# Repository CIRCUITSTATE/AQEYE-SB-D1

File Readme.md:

# AQEYE-SB-D1

[**AQEYE-SB-D1**](https://github.com/CIRCUITSTATE/AQEYE-SB-D1) is a PCB designed to hold the sensors for the AQEYE-D1 Air Quality Monitor project by CIRCUITSTATE Electronics. The board is designed to be connected to either the [**ESP32-S3-Touch-LCD-2.8**](https://www.waveshare.com/esp32-s3-touch-lcd-2.8.htm) from Waveshare or the AQEYE-MB-D1 main board. A separate sensor board was designed to keep the sensitive components away from external interferences such as noise, heat and other effects. This also makes it easier to replace the sensors or to add new sensors in the future without having to redesign the main board. AQEYE-SB-D1 is a completely open-source hardware (OSHW) project designed in the **KiCad** open-source EDA tool. **SB** stands for Sensor Board and **D1** is the first design variant of this project. You can download the source files of this design, modify them and redistribute them as you wish.

## Features

- Sensors
  - **Asair DHT20** temperature and humidity sensor.
  - **Asair AGS02MA** TVOC (Total Volatile Organic Compounds) sensor.
  - **Winsen ZH06** PM (Particulate Matter) sensor with PM1.0, PM2.5, PM10 measurement.
  - **Sensirion SCD40-D-R2** CO2 (Carbon Dioxide) sensor.
  - **Sensirion SGP40-D-R4** TVOC sensor.
- Connectors and solderpads for all sensors.
- 12-pin JST-SH connector for connecting to the main board.
- Selectable I2C pull-up resistors.
- **TPS61023** +5V boost converter to generate 5V from the 3.3V input for sensors that require 5V.
  - Output controlled by a GPIO pin.
- **AP22804AW5** based +3.3V load switch to control the power.
  - Controlled by a GPIO pin.
  - Jumper pad to constant enable.
- **LM66100DCKR** ideal diode based voltage ORing selector and reverse polarity protection for the 5V rail.
- Power indication LEDs for both 3.3V and 5V rails.
- Four M2 mounting holes.

## Design

- **Parent Project:** AQEYE-SB
- **Variant:** [AQEYE-SB-D1](https://github.com/CIRCUITSTATE/AQEYE-SB-D1)
- **Author:** Vishnu Mohanan (@vishnumaiea, @vizmohanan)
- **Latest Revision:** `R0.1`
- **Layer Count:** 2
- **Thickness:** 1.6 mm
- **Dimensions:** 80 x 30 mm
- **EDA Tool:** KiCad V9
- **License:** MIT

## Contributing

If you would like to contribute this project, you are welcome to post issues and feature requests on the **Issues** page. If you fork this project and created a new variant, you can let us know about it and get a unique identifier assigned for your project. The ID takes the following form.

```
Y<digit><letter><digit>
```

`Y` – Constant prefix.

`<digit>` – Digits from 0–9

`<letter>` – Characters from A–Z.

**Examples:**

```
Y1A1
Y1A2
Y2B1
Y3C4
```

The forked project should then be renamed to `AQEYE-SB-D1-<ID>` form.

**Guidelines:**

- IDs are assigned upon request. You can create a new issue to request a new ID once a fork is created. Keep the issue title as `Request New ID` and include a link to your fork in the description.
- You can either request a new ID that you like and that is already not chosen, or allow us to choose an ID for you.
- You should rename the original source files with the `AQEYE-SB-D1-<ID>` format.
- On the PCB, you can place the name of the project as `AQEYE-SB-D1` and keep the ID as a standalone text on any visible layers.
- Once a unique ID is assigned to a forked project, the revision should be reset to `R0.1`. Do not keep the original revision of the project.

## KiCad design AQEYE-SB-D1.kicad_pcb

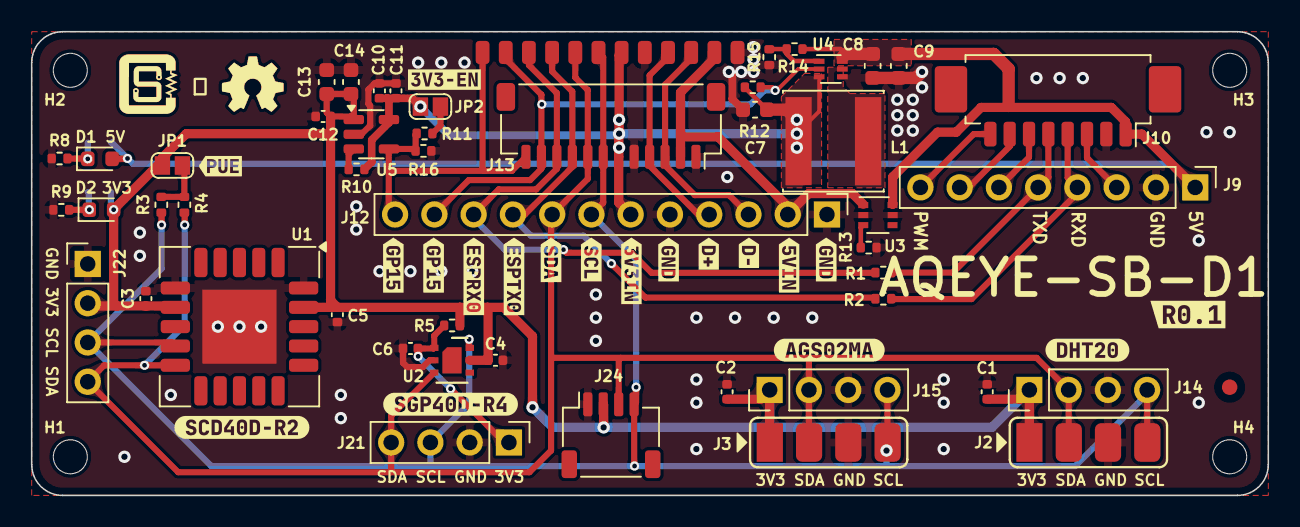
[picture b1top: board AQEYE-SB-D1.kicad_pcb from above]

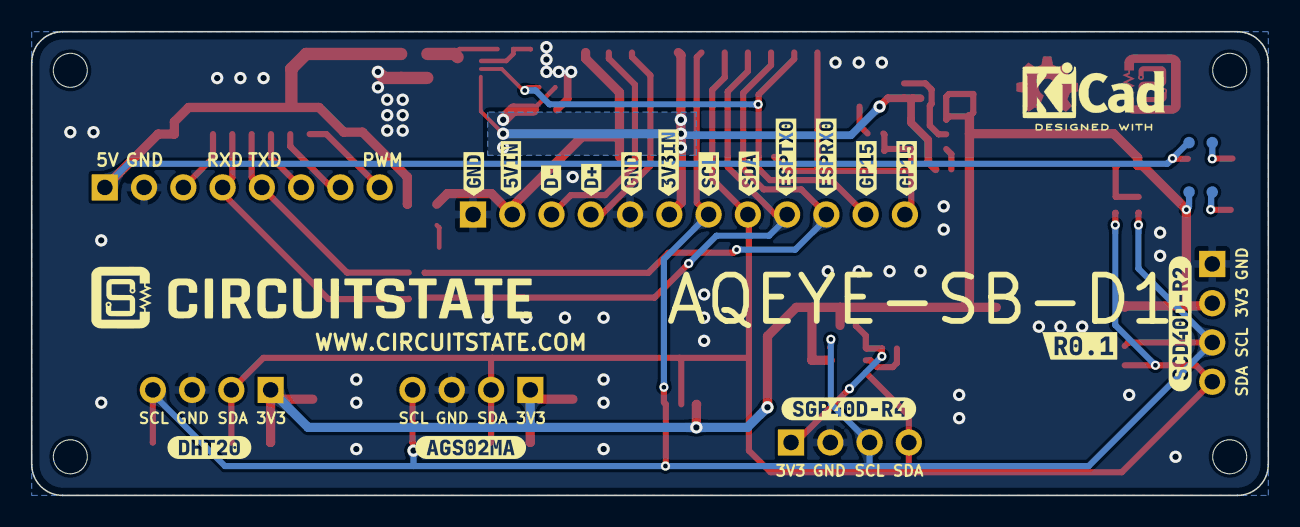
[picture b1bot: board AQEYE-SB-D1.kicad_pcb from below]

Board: 2 copper layers, 80.0 x 30.0 mm, 105 parts (21 on the bottom side), 24 nets.

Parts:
C1, C2, C3, C5, C10, C12: 0.1uF; C_0402_1005Metric
C4, C6, C11: 10uF; C_0402_1005Metric
C7, C8, C9, C13, C14: 22uF; C_0603_1608Metric
D1: 5V_LED; LED_0603_1608Metric
D2: 3V3_LED; LED_0603_1608Metric
H1, H2, H3, H4: Mounting Hole; MountingHole_2.2mm_M2_DIN965
J1: GPIO15; Solderpad_Rounded_Rectangle_0.9x1.5mm
J2: DHT20_PAD; Solderpad_1x04_P2.54mm_Rounded_Rectangle
J3: AGS02MA_PAD; Solderpad_1x04_P2.54mm_Rounded_Rectangle
J4: GPIO18; Solderpad_Rounded_Rectangle_0.9x1.5mm
J5: ESP_RXD0; Solderpad_Rounded_Rectangle_0.9x1.5mm
J6: ESP_TXD0; Solderpad_Rounded_Rectangle_0.9x1.5mm
J7: I2C_SDA; Solderpad_Rounded_Rectangle_0.9x1.5mm
J8: I2C_SCL; Solderpad_Rounded_Rectangle_0.9x1.5mm
J9: ZH06_Pin; PinHeader_1x08_P2.54mm_Vertical
J10: ZH06_PicoBlade; Molex_PicoBlade_53261-0871_1x08-1MP_P1.25mm_Horizontal
J11: +3.3V; Solderpad_Rounded_Rectangle_0.9x1.5mm
J12: MB_PINS; PinHeader_1x12_P2.54mm_Vertical
J13: MB_CONNECTOR; JST_SH_SM12B-SRSS-TB_1x12-1MP_P1.00mm_Horizontal
J14: DHT20; PinHeader_1x04_P2.54mm_Vertical
J15: AGS02MA; PinHeader_1x04_P2.54mm_Vertical
J16, J20: GND; Solderpad_Rounded_Rectangle_0.9x1.5mm
J17: USB_D+; Solderpad_Rounded_Rectangle_0.9x1.5mm
J18: USB_D-; Solderpad_Rounded_Rectangle_0.9x1.5mm
J19: +5V; Solderpad_Rounded_Rectangle_0.9x1.5mm
J21: SGP40-D-R4_CONN; PinHeader_1x04_P2.54mm_Vertical
J22: SCD40-D-R2_CONN; PinHeader_1x04_P2.54mm_Vertical
J24: STEMMA-QT; JST_SH_SM04B-SRSS-TB_1x04-1MP_P1.00mm_Horizontal_2
JP1: I2C_PUE; Solder-Jumper-1x2_P1.3mm_Open_Rounded_1.0x1.2mm
JP2: 3V3_EN; Solder-Jumper-1x2_P1.3mm_Open_Rounded_1.0x1.2mm
L1: 1uH; L_Changjiang_FNR6020S
R1, R2, R11: 1K; R_0402_1005Metric
R3, R4: 5.1K; R_0402_1005Metric
R5: 4.7R; R_0402_1005Metric
R8: 330R; R_0402_1005Metric
R9: 220R; R_0402_1005Metric
R10, R12, R13, R16: 10K; R_0402_1005Metric
R14: 732K; R_0402_1005Metric
R15: 100K; R_0402_1005Metric
TP1: 5V_LED_P; TestPoint-0.75mm
TP2: 5V_LED_M; TestPoint-0.75mm
TP3: 3V3_LED_P; TestPoint-0.75mm
TP4: 3V3_LED_M; TestPoint-0.75mm
U1: SCD40-D-R2; Sensirion_SCD4x-1EP_10.1x10.1mm_P1.25mm_EP4.8x4.8mm
U2: SGP40-D-R4; DFN-6-1EP_2.44x2.44mm_P0.8mm_EP1.25x1.7mm
U3: LM66100DCKR; SOT-363_SC-70-6
U4: TPS61023; SOT-563
U5: AP22804AW5; SOT-23-5
kibuzzard-68408B8A, kibuzzard-68408B8A#2: G***; kibuzzard-68408B8A
kibuzzard-68408BAF, kibuzzard-68408BAF#2: G***; kibuzzard-68408BAF
kibuzzard-68408BD4, kibuzzard-68408BD4#2: G***; kibuzzard-68408BD4
kibuzzard-68408D06, kibuzzard-68408D06#2: G***; kibuzzard-68408D06
kibuzzard-68408D87, kibuzzard-68408D87#2: G***; kibuzzard-68408D87
kibuzzard-68408E5C: G***; kibuzzard-68408E5C
kibuzzard-68408E86: G***; kibuzzard-68408E86
kibuzzard-684088E7, kibuzzard-684088E7#2, kibuzzard-684088E7#3, kibuzzard-684088E7#4: G***; kibuzzard-684088E7
kibuzzard-6840890A, kibuzzard-6840890A#2, kibuzzard-6840890A#3, kibuzzard-6840890A#4: G***; kibuzzard-6840890A
kibuzzard-6840894F, kibuzzard-6840894F#2: G***; kibuzzard-6840894F
kibuzzard-6840895D, kibuzzard-6840895D#2: G***; kibuzzard-6840895D
kibuzzard-68408942, kibuzzard-68408942#2: G***; kibuzzard-68408942
kibuzzard-68408956, kibuzzard-68408956#2: G***; kibuzzard-68408956
kibuzzard-68408963, kibuzzard-68408963#2: G***; kibuzzard-68408963
kibuzzard-68408966, kibuzzard-68408966#2: G***; kibuzzard-68408966
kibuzzard-68408979, kibuzzard-68408979#2: G***; kibuzzard-68408979
kibuzzard-68408981, kibuzzard-68408981#2: G***; kibuzzard-68408981

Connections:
+3.3V: C1.1, C2.1, C3.1, C4.1, C5.1, C12.1, C13.1, C14.1, D2.2 (A), J2.1, J3.1, J14.1, J15.1, J22.2, J24.2, JP1.1 (A), R5.1, TP3.1, U1.7 (VDD), U1.19 (VDD), U2.5 (VDDH), U5.1 (OUT)
+3.3V_IN: C7.1, C10.1, C11.1, J11.1, J12.6, J13.6, JP2.2 (B), L1.1, R10.2, R12.2, U4.3 (VIN), U5.5 (IN)
+5V: C8.1, C9.1, D1.2 (A), J9.1, J10.1, R14.2, TP1.1, U3.6 (VOUT), U4.6 (VOUT)
+5V_IN: J12.2, J13.2, J19.1, U3.1 (VIN)
/ESP_RXD0: J5.1, J12.10, J13.10, R1.2
/ESP_TXD0: J6.1, J12.9, J13.9, R2.2
/GPIO15: J1.1, J12.12, J13.12, R11.1, R16.2, U5.4 (EN)
/GPIO18: J4.1, J12.11, J13.11, R12.1, U4.2 (EN)
/I2C_SCL: J2.4, J3.4, J8.1, J12.7, J13.7, J14.4, J15.4, J21.3, J22.3, J24.4, R3.1, U1.9 (SCL), U2.6 (SCL)
/I2C_SDA: J2.2, J3.2, J7.1, J12.8, J13.8, J14.2, J15.2, J21.4, J22.4, J24.3, R4.1, U1.10 (SDA), U2.3 (SDA)
/USB_D+: J12.4, J13.4, J17.1
/USB_D-: J12.3, J13.3, J18.1
GND: C1.2, C2.2, C3.2, C4.2, C5.2, C6.1, C7.2, C8.2, C9.2, C10.2, C11.2, C12.2, C13.2, C14.2, J2.3, J3.3, J9.2, J10.2, J12.1, J12.5, J13.1, J13.5, J14.3, J15.3, J16.1, J20.1, J21.2, J22.1, J24.1, R8.1, R9.1, R13.1, R15.1, R16.1, U1.6 (GND), U1.20 (GND), U1.21 (GND), U2.2 (GND), U3.2 (GND), U3.5 (ST), U4.4 (GND), U5.2 (GND)
unnamed: D1.1 (K), R8.2, TP2.1
unnamed: D2.1 (K), R9.2, TP4.1
unnamed: J9.4, J10.4, R2.1
unnamed: J9.5, J10.5, R1.1
unnamed: C6.2, J21.1, R5.2, U2.1 (VDD)
unnamed: JP1.2 (B), R3.2, R4.2
unnamed: JP2.1 (A), R11.2
unnamed: R13.2, U3.3 (CE)
unnamed: R14.1, R15.2, U4.1 (FB)
unnamed: L1.2, U4.5 (SW)
unnamed: R10.1, U5.3 (~FLG)

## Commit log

2025-06-05 Initial commit
    - Schematic
    - Completed the schematic.
    - Assigned all footprints.
    - Added net classes and colors.
    - ERC passes.
    - PCB
2025-06-06 Generated manufacturing files
    - Schematic
    - Updated BoM.
    - Assigned all MPNs.
    - Added `Group by MPN-DNP` preset.
    - PCB
    - Imported all changes to the PCB.
2025-06-07 Added 5V boost converter
    - Schematic
    - Realized that the main board can not supply 5V when the USB is not connected.
    - Added a `TPS61023` 5V boost converter to generate 5V from the 3.3V input.
    - Removed the 5V load switch since the 5V output can not be controlled via the boost converter.
    - The 5V converter enabled by default with a GPIO control.
    - Added `LM66100DCKR` single-channel ideal diode to connect the VBUS to the 5V rail.
2025-06-15 Updated Readme
    - Added poster image.
    - Generated PCB renders without the Asair sensors.
2025-06-15 Added License file
2025-06-22 Added new banner image
